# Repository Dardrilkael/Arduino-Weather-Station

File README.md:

<div align="center">
	
	<br/>
	<br/>
</div>

# MeteoroSense
## Sistema Embarcado para captação de dados meteorológicos

Este repositório contém o código-fonte de um sistema integrado de gestão meteorológica para a Universidade Federal do Rio de Janeiro (UFRJ).

## Como usar

Para usar o sistema, você precisará:

1. Clonar o repositório.
2. Instalar as dependências.
3. Configurar o sistema.

Para obter mais informações, consulte a documentação do sistema.

# Circuitos

Para esse projeto, desenvolvemos uma placa customizada baseada no microcontrolador ESP-32. Esta placa foi concebida com o intuito específico de atender às exigências do projeto, proporcionando um conjunto abrangente de funcionalidades para a coleta e processamento de dados meteorológicos. Integrando uma gama de sensores e um design eficiente, a placa oferece um desempenho excepcional. Além disso, sua arquitetura versátil permite uma fácil integração com outros componentes do sistema, tornando-a uma escolha ideal para otimizar a operação.

Dedicamos atenção especial à economia de recursos durante o processo de fabricação, visando minimizar os custos de produção. Implementamos estratégias para alcançar esse objetivo, sem comprometer a qualidade ou desempenho da placa. Isso resultou em uma solução acessível e viável, permitindo uma ampla utilização em diversas aplicações meteorológicas, desde projetos pessoais até implantações em larga escala.

<div align="center">
	
	<br/>
	<br/>
</div>

## Contato

Para mais informações, entre em contato com o autor do projeto:

# Dependencias externas
 * [DHT-sensor-library](https://github.com/adafruit/DHT-sensor-library)
 * [NTPClient](https://github.com/arduino-libraries/NTPClient)
 * [PubSubClient](https://github.com/knolleary/pubsubclient)
 * [Adafruit_BMP085](https://github.com/adafruit/Adafruit-BMP085-Library)
 * [DHT-sensor-library](https://github.com/adafruit/DHT-sensor-library)
 * [ArduinoBLE](https://github.com/arduino-libraries/ArduinoBLE)
 * [Aduinojson](https://arduinojson.org/?utm_source=meta&utm_medium=library.properties)

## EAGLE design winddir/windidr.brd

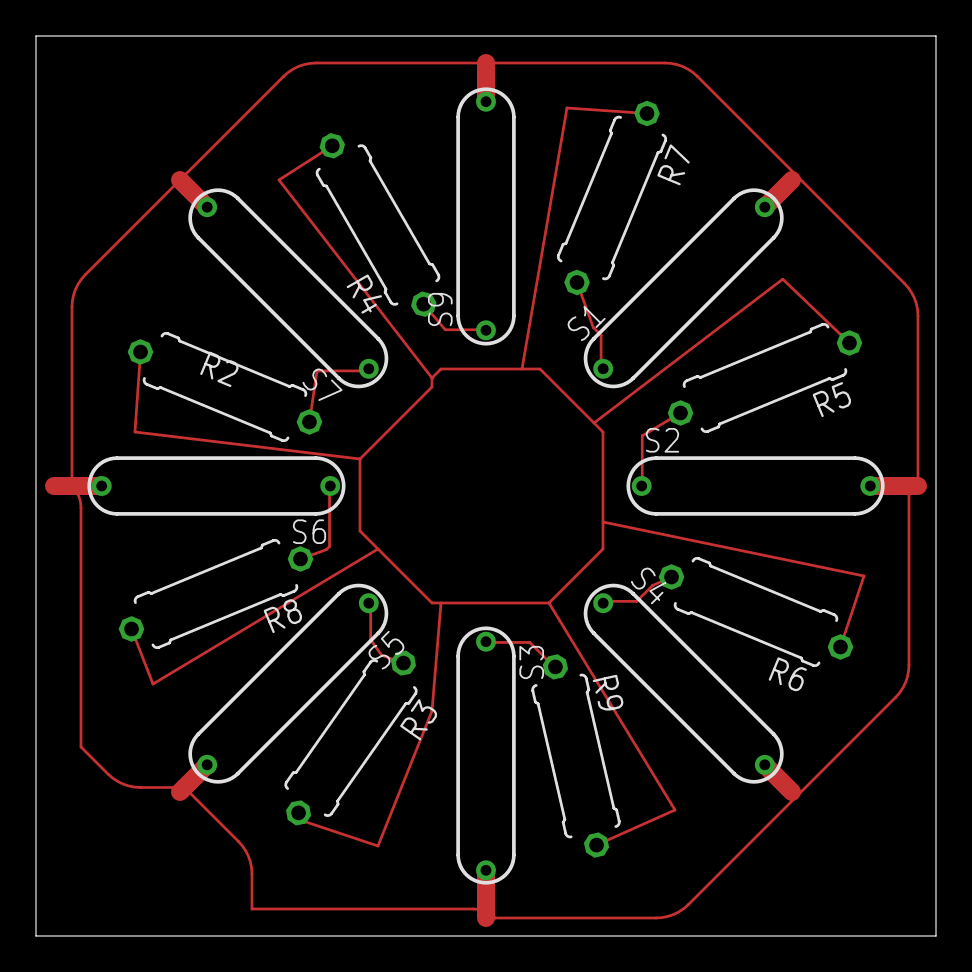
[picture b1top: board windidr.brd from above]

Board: 2 copper layers, 50.0 x 50.0 mm, 16 parts (0 on the bottom side), 9 nets.

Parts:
R2, R3, R4, R5, R6, R7, R8, R9: 0309/10
S1, S2, S3, S4, S5, S6, S7, S9: REED-SWITCH-MK6-5-B; MK6-5

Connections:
unnamed: R4.1, S9.1
unnamed: R6.2, S4.1
unnamed: R3.1, S5.1
unnamed: R2.2, S7.1
unnamed: R5.2, S2.1
unnamed: R7.2, S1.1
unnamed: R8.1, S6.1
unnamed: R9.1, S3.1
OUT: S1.2, S2.2, S3.2, S4.2, S5.2, S6.2, S7.2, S9.2

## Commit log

2025-01-23 feat: Initial sensors test
2025-01-23 Improve code
2025-01-23 feat: added bluetooth
2025-01-23 Watchdog
2025-01-23 moved mqtt and begin OTA
2025-01-23 Added pch.h and update OTA
2025-01-23 remove second broker
2025-01-23 file retrieval
2025-01-23 added docs
2025-04-19 chore: random things
2025-05-03 refactor(config): remove second mqtt configuration
2025-05-03 Inital test of http sending
2025-05-03 chore: minor changes
2025-05-03 fix: http file retrieval
2025-05-03 fix: update FIRMWARE_VERSION
2025-05-05 chore: changed http server
2025-05-08 chore: change http backup server to metcolab
2025-05-08 fix: logging
2025-05-08 chore: http change start_time and add interval macro
2025-05-08 feat: add health check data publishing to MQTT
2025-05-08 fix: update firmware version and increase HTTP backup interval to 40s
2025-05-08 feat: include timestamp in health check MQTT message
2025-05-08 fix: handle WiFi disconnection and automatic reconnection in loop
2025-05-08 fix: correct firmware version to 3.0.15 in OTA.h
2025-05-08 fix: update filename check to include '.txt' extension for today's date
2025-05-14 feat: implement data.h
2025-05-19 fix: update firmware version to 3.0.154 and adjust VANE_PIN definition fix: correct server URL configuration in httpRecover.cpp fix: increase HTTP backup interval from 40000 to 80000 ms
2025-05-20 fix: update firmware version to 3.0.155 and correct DHTPIN definition
2025-05-20 fix: update firmware version to 3.0.156w and add wind direction sampling functionality
2025-05-20 fix: update firmware version to 3.0.156 and correct server URL in httpRecover.cpp
2025-06-06 fix: comment out WiFi reconnection logic and adjust LED control in loop function
2025-06-13 fix: wifi reconnect
2025-06-24 fix: update firmware version to 3.0.1582 and improve WiFi disconnection logic
2025-06-26 fix: update firmware version to 3.0.1583, add deleteFile function, and log reset reason in JSON payload
2025-06-27 fix: update firmware version to 3.0.1585 and add debug comments in index.ino
2025-06-27 fix: update loop function to log timestamp and formatted time on WiFi disconnection
2025-06-27 fix: update firmware version to 3.0.1586
2025-06-27 fix: update firmware version to 3.0.1587 and log reset reason in setup
2025-06-27 fix: update firmware version to 3.0.1588 and improve logging on WiFi disconnection
2025-06-28 fix: update sensor variables to volatile and optimize anemometer change handling
2025-06-28 fix: update (forgotten) sensor variables to volatile for improved concurrency handling
2025-06-29 fix: add BLE2902 descriptor to health characteristic and remove unused MQTT V2 fields
2025-06-30 fix: update firmware version to 3.0.1591 and improve health check logging
2025-07-04 fix: enhance file handling by adding content type detection and updating sendCSVFile function signature
2025-07-04 Refactor code for improved readability and debugging
    - Updated logging mechanism to use logDebug functions instead of OnDebug for better control over debug output.
    - Cleaned up whitespace and formatting across multiple files for consistency.
    - Enhanced MQTT class with better memory management and logging for publish and connection methods.
    - Improved SD card handling functions with clearer logging and error messages.
    - Refined sensor handling and initialization functions for better clarity and maintainability.
    - Removed unnecessary comments and dead code to streamline the codebase.
2025-07-04 fix: improve MQTT JSON handling and buffer management in publishJsonResponse and mqttSubCallback functions
2025-07-22 feat: add sensor management and MQTT client for weather station data handling
2025-07-22 test notyfications
2025-07-22 fix: minor erros
2025-07-23 feat: enhance sendCSVFile function to include command ID and handle empty URL
2025-07-23 updated FIRMWARE_VERSION to 3.0.161
2025-07-29 fix: update firmware version to 3.0.162 and improve sensor reset handling
2025-07-29 feat: update firmware version to 3.0.163 and implement timer structure for improved interval management
2025-07-29 refactor: clean up formatting and improve readability in sendCSVFile function
2025-07-29 chore: update firmware version to 3.0.164 and comment out brown-out register write in setup function
2025-07-29 refactor: improve code formatting and readability in Sensors and sd-repository headers
2025-08-08 feat: enhance sensor data handling
2025-08-08 fix: correct health check time remaining calculation using timerMain
2025-08-08 refactor: enhance SD_BLINK function and improve error handling in MQTT and WIFI string parsing
2025-08-08 fix: update processFiles function to correctly handle today's file name and success flag
2025-08-08 refactor: update DHT lib for esp32
2025-08-08 updated version
2025-08-08 refactor: enhance OTA update function to include progress callback and improve error handling
2025-08-13 refactor: replace SD_BLINK function with morseCode for improved readability and functionality
2025-08-21 refactor: update OTA functions to return OTA_Result for improved error handling and status reporting
2025-09-11 refactor: enhance SD card handling functions and add sensor paramtrization support from json(SD)
2025-09-12 Fixing
2025-09-12 fix: compialtion error
2025-09-12 increase heatthcheck time to 10s and wifi retry to 60s
2025-09-14 refactor: remove unused string include and add debug conditional for Serial.begin
2025-09-17 chore: update firmware version to 3.0.175 and add delays for stability
2025-09-17 fix: add delays in loop and WiFi reconnection for stability
2025-09-22 to be deleted
2025-10-04 feat: implement ModemAT and change MQTT class to work is cellular
2025-10-04 refactor: change apn declaration from constexpr to const and remove redundant setupNetwork function
2025-10-04 feat: implement NTP client with timezone handling and synchronization logic
2025-10-06 just testing
2025-11-25 fix: update esp core to 3.3.3 and correct errors
2025-11-25 Bmp temp priority
2025-11-26 feat: update firmware version to 3.0.177 and implement TimeManager and WifiManager classes for improved time handling and WiFi management
2025-12-20 Refactor HTTP client implementation to use ATResponse
    - Added HttpClient class to manage HTTP requests using AT commands.
    - Implemented methods for GET and POST requests, including multipart uploads.
    - Replaced previous HTTPClient usage with the new HttpClient class in httpRecover.cpp.
    - Updated index.ino to initialize and use the new HttpClient class.
    - Refactored MQTT class to remove dependency on PubSubClient and WiFiClient, using AT commands instead.
    - Improved MQTT connection management and message handling.
2026-03-20 Remove obsolete EAGLE AutoRouter job and statistics files from the winddir directory. These files are no longer needed and have been deleted to clean up the project.
2026-03-20 fix: update BLE::updateValue method signature to accept characteristicId as std::string
2026-03-20 fix: improve float handling in parseData function to return "null" for NaN values
2026-03-20 fix: resolve dangling pointer issue in CharacteristicsCallback and improve updateValue method
2026-03-20 fix: correct timer initialization and update timestamp handling to support 64-bit time_t
2026-03-20 fix: enhance NTP synchronization handling and add isTimeSynced method to TimeManager
2026-03-20 fix: remove unnecessary #pragma once directive from httpRecover and sd-repository files
2026-03-21 fix: replace heap allocation with stack buffers in parseMQTTString and parseWIFIString to prevent memory leaks and improve safety
2026-03-21 fix: remove unused WiFiClient from WifiManager to streamline code
2026-03-21 fix: change startTime and now variables to unsigned long to prevent signed overflow issues
2026-03-21 fix: update timestamp fields to use time_t
2026-03-21 fix: move logIt function declaration to pch.h and ensure proper inclusion of <string>
2026-03-21 fix: remove default value for store parameter in logIt function to enforce explicit usage
2026-03-21 fix: update updateWindGust method to use unsigned long and add interrupt guard for anemometerCounter
2026-03-21 fix: change chunkSize to constexpr for safety and update OTA restart logic to prevent reboot on failed updates
2026-03-21 refactor: remove unused csvHeader variable and include httpRecover.h in index.ino
2026-03-21 feat: implement log buffering for SD writes to improve performance and reduce wear
2026-03-21 fix: update wind speed and gust calculations with calibration factors for accuracy
2026-03-21 feat: implement command handling and file transfer via MQTT with JSON responses
2026-03-21 fix: update firmware version to 3.0.178
2026-03-23 chore: remove unused index.rar file
2026-03-25 feat: Add command handling and MQTT integration
    - Introduced Commands.h for command execution and MQTT subscription handling.
    - Updated OTA version to 3.0.178 and commented out OTA update code for debugging.
    - Modified Sensors class to handle unsigned long for time-related functions.
    - Enhanced data parsing functions to use snprintf for safer string handling.
    - Refactored HealthCheck and Metrics structures to use time_t for timestamps.
    - Improved MQTT string parsing to avoid heap allocation and potential memory leaks.
2026-03-25 feat: Implement file transfer and command execution via MQTT with JSON responses
2026-03-25 feat: add syncFromModemCCLK method to synchronize time from modem CCLK format
2026-03-25 fix: update MQTT callback function signatures to use const qualifiers for topic and payload
2026-03-27 feat: implement shared mailbox for BLE commands to improve asynchronous handling
2026-03-27 syncFromModemCCLK: pointer arithmetic before NULL check
2026-03-27 fix: move watchdogRTC call higher in setup to ensure proper watchdog functionality
2026-03-27 fix: optimize getMeasurements by adjusting counters atomically and removing unnecessary reset
2026-03-27 fix: remove uncesary timer add a second feed for the RTCwatchdog in the main loop
2026-03-27 feat: implement BLE task for handling commands asynchronously with mailbox support
2026-04-21 fix: clean up log messages and add connected() method in MQTT class
